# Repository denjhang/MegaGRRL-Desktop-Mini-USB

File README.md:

# MegaGRRL-Desktop-Mini-USB
 I have been using the desktop version of MegaGRRL for 4 years. As my PCB drawing skills improve, I have the confidence to realize all my ideas and changes. This version is based on the Type-C version and includes a lot of practical modifications.Note that for convenience, I only modified the PCB and not the schematic.    
The latest version: MegaGRRL Desktop DJ V0.5.  
It has been hardware verified and can be used.  
## Improvements of Type-C version :  
1. Use CH340C to replace CH340G to save crystal  
2. Use 2SC1815 to replace diode to get full CH340 serial port function (SPFM Lite compatibility)  
3. PCA9634D is difficult to buy, replaced with PCA9634PW.  
4. Use Type-C to replace USB-B.
5. Remaining issue: The solder pad of the 3.5mm headphone jack is too small.  
 ## Details of improvements to my version :   
1. Delete the 7805, 78M33, and other antique LDO step-down chips, as well as the huge heat sink, which are inefficient and generate a lot of heat. I used a newly designed SPFM Lite power supply circuit to replace it.  
2. Use an isolated voltage regulator module such as IB0905/0505S to achieve step-down/regulation, so the PCB currently supports 5V or 9V input, depending on the model of the voltage regulator module. B0905/0505 can be easily obtained on AliExpress. These voltage regulator modules work well on SPFM Lite, with very little power supply noise, which can further improve the sound quality.(Outdated)  
3. Delete MOSFETs such as IRF9530, which are huge and too retro.  
4. Use F0805 to protect the power circuit.  
5. Use a strong PS-22E05 (A04) self-locking switch to replace the original small switch to extend the life of the power button.  
6. All micro switches use white patch 6*6 silicone buttons, which do not require circuit modification and can significantly improve the user experience. The original micro switches made my hands hurt.
7. Because some buyers reported that the main volume potentiometer was easily damaged during transportation, I replaced it with RK097 B10K. RK097 is smaller and more robust, and the entire potentiometer is plastic-sealed, which is more reliable.  
8. Delete the 3296 potentiometer.  
9. In order to make the SN76489 volume adjustable, add an RK097 to adjust its volume, and replace R6/R8 with 47K.  
10. Replace the difficult-to-solder Type-C with Mini-USB.  
11. Restore natalie's silk screen art, obtained by reverse engineering the original desktop motherboard. (Actually not necessary)  
12. Double-layer square hole IC socket ensures good connection and service life. (No need to modify the PCB)  
13. Solder the round hole female header first in RN2 and then insert the resistor (no need to modify the PCB) to facilitate mass production and upload factory firmware.  
14. Add my silk screen art "Denjhang's OSHW"  
15. Optional self-ejecting SD card slot or self-ejecting TF card slot, more flexible to choose the type of memory card, protecting the memory card while further improving the user experience.  
16. Use "Mini560" high efficiency DC-DC step-down module to replace B0905/0505, it works very well so far, supports 9/12V input, and generates almost no heat. Mini560 can be easily purchased at Alex and is cheap.
17. Use the correct PJ-306/3F07 headphone jack package to replace the incorrect package in the Type-C version.
18. Added keyboard connector. Can be used to connect Cherry switches, MegaDrive controllers, wireless remote controls, etc. It can also be connected to the top keyboard of the acrylic case.  
 ## To do  
1. Design and make the acrylic shell, which is done by Xiaohao Studio (completed)  
2. Design a new MegaGRRL-modular motherboard to completely separate the data and analog lines and reduce interference noise. (completed)  
3. USB/DC dual power supply, refer to SPFM Lite circuit (completed)  
4. Compatible with RE:Birth module. (completed)  
5. Add battery interface. (completed)

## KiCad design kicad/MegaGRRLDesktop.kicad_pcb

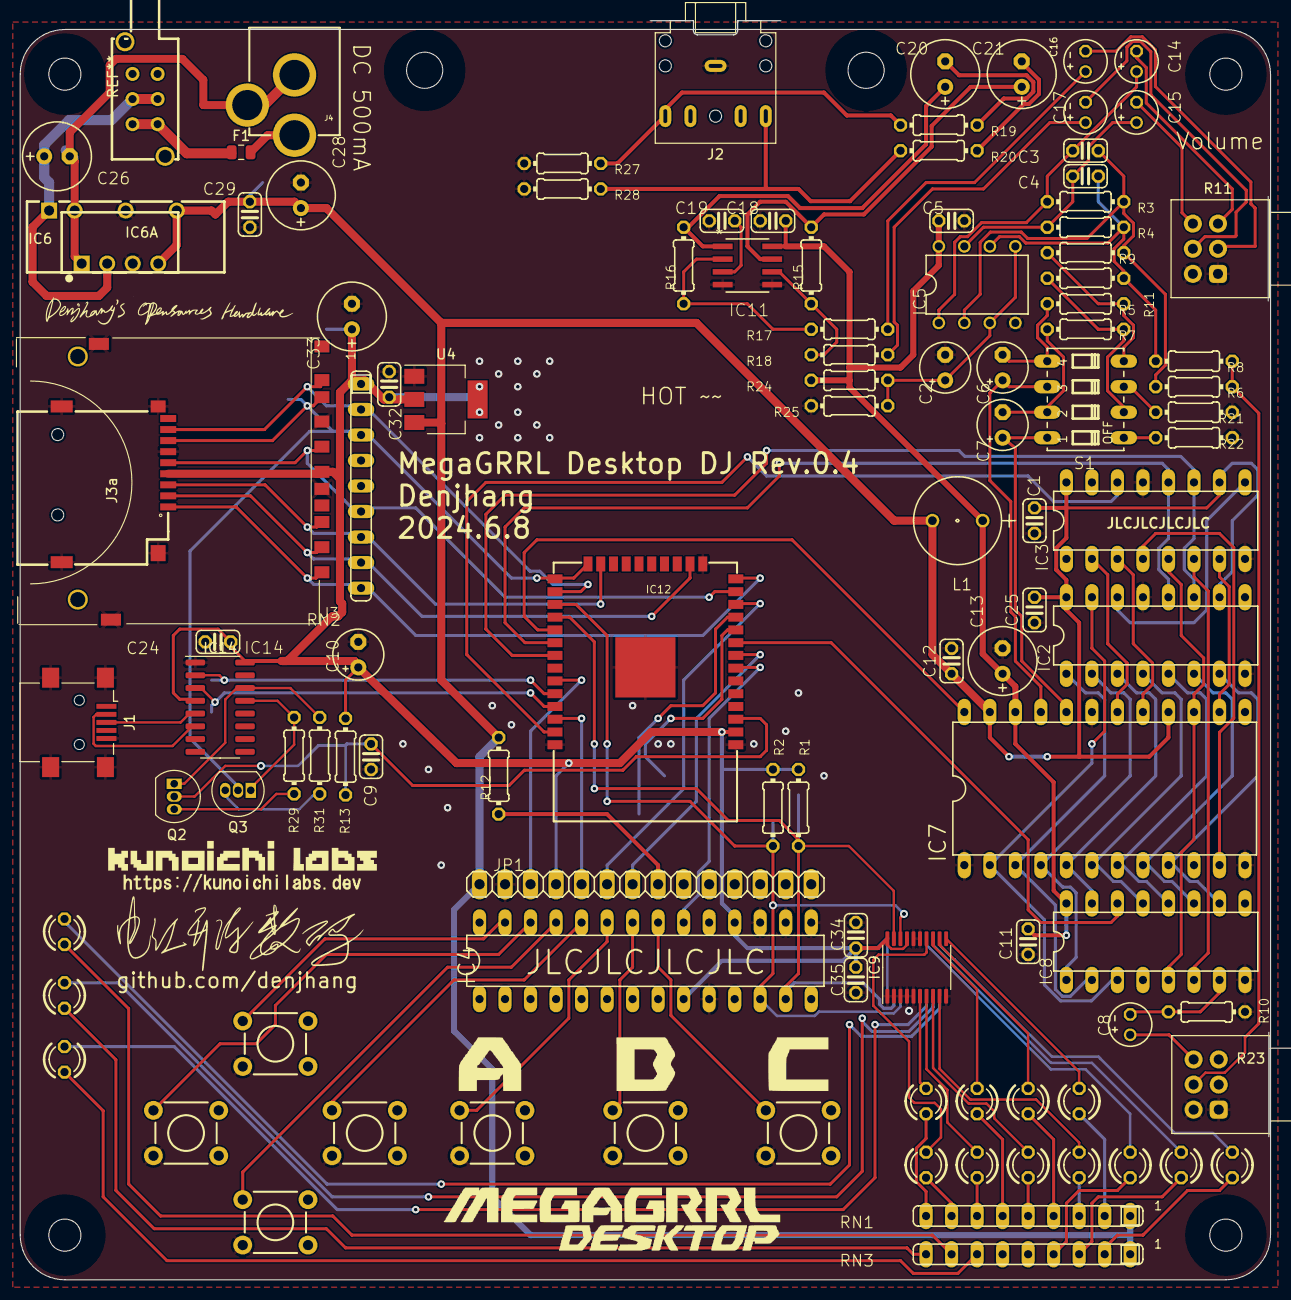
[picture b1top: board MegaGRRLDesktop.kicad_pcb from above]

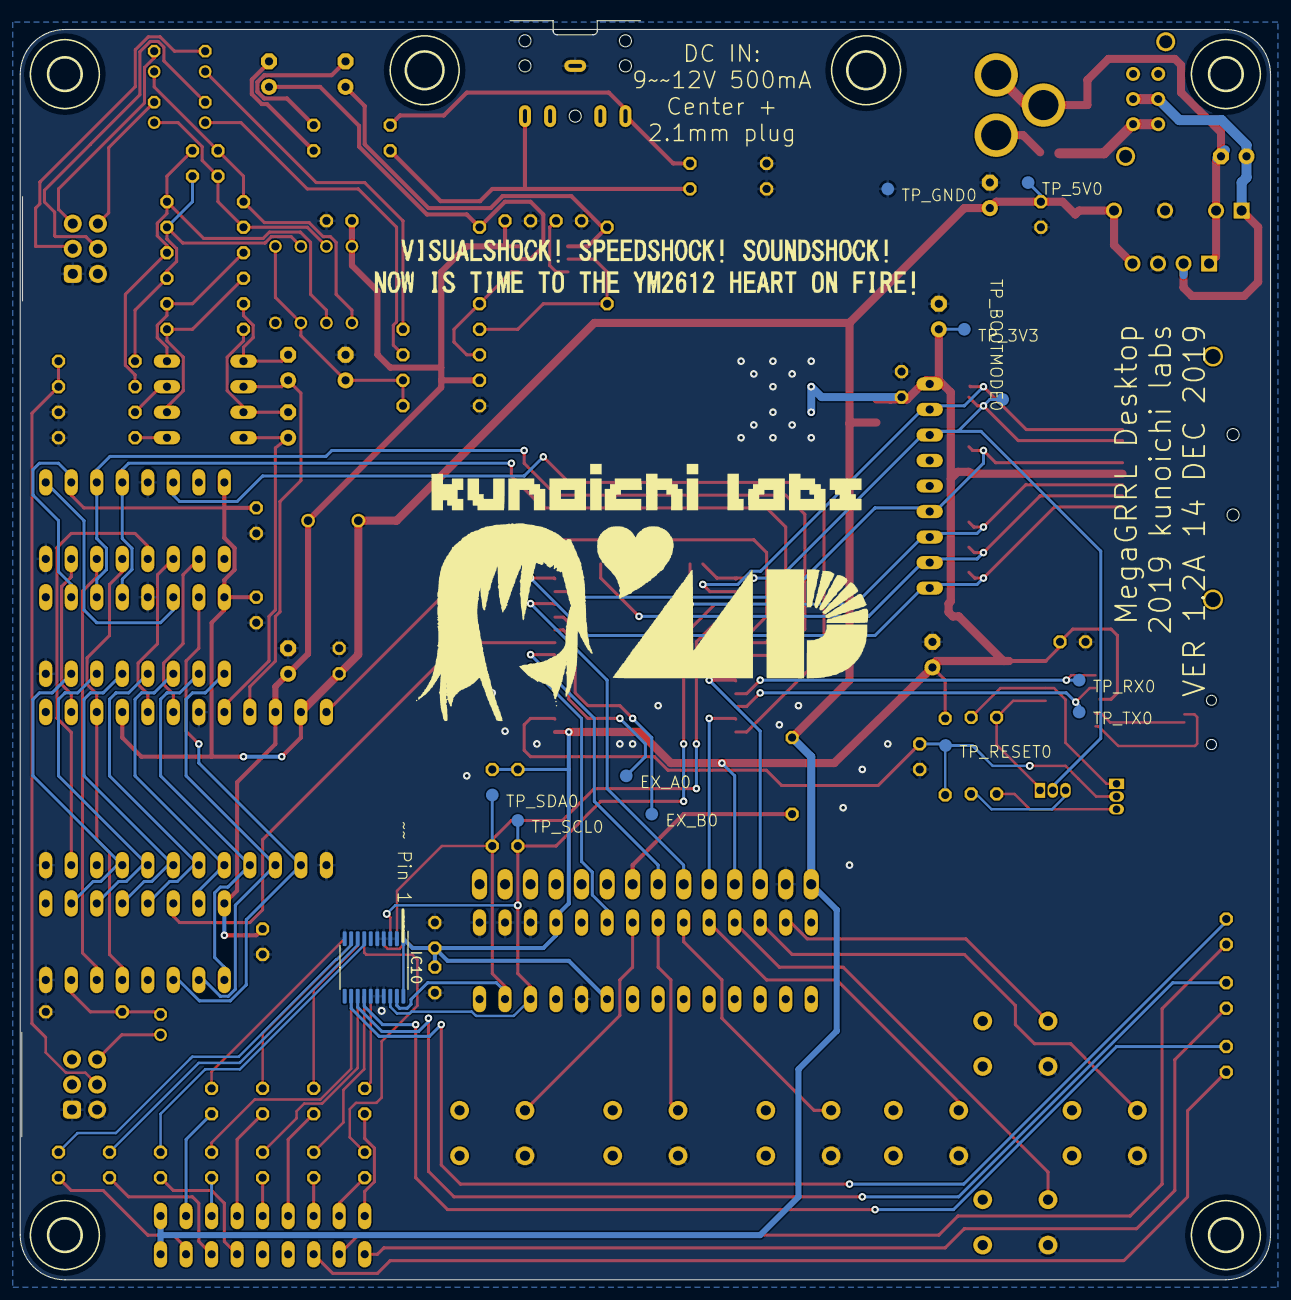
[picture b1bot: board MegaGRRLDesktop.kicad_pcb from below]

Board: 2 copper layers, 124.5 x 125.3 mm, 125 parts (18 on the bottom side), 118 nets.

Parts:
C1, C5, C9, C11, C12, C18, C19, C24, C25, C29, C32, C34, C35: 0.1uF; C025-024X044
C2, C6, C7, C10: 10uF; E2,5-5
C3, C4: 120pF; C025-024X044
C8, C14, C15, C16, C17: 1uF; E2-4
C13: 330uF; E2,5-7
C20, C21, C26, C28, C33: 100uF; E2,5-7
EX_A0: B1,27
EX_B0: B1,27
F1: Fuse_0805_2012Metric
H3, H4, H7, H8: MOUNT-HOLE3.2; 3,2
H5, H6: MOUNT-HOLE3.6; 3,6
IC2, IC3: 74HCT595N; DIL16
IC4: MCP23017SP; DIL28-3
IC5: NE5532N; DIL08
IC6: std:a4c6558b222b489b868198a352481a86; PWRM-TH_B0505S-3WR2
IC6A: std:44d60e1deb274ae4bbd12617d1f88879; PWRM-TH_BXXXXS-1W
IC7: YM2612
IC8: SN76489
IC9, IC10: PCA9634PW; TSSOP-20_4.4x6.5mm_P0.65mm
IC11: TPA6111A2DR; D8
IC12: ESP-WROOM-32ESP-WROOM-32-NO-RF; ESP-WROOM-32-NO-RF
IC14: CH340C; SOIC-16_3.9x9.9mm_P1.27mm
J1: USB_B_Mini; USB_Mini-B_Lumberg_2486_01_Horizontal
J2: 35RAPC4BHN2; Jack_3.5mm_CUI_SJ1-3525N_Horizontal
J3: 2041021-3; SD-106M
J3a: std:8630a74813a14cdca67e7b05dd5d2bc3; TF-SMD_TF-PUSH
J4: POWER_JACK; POWER_JACK_PTH
JP1: ILI9341_2_4
L1: RL622-101K-RC; RL622_SERIES
LED1, LED2, LED3, LED4, LED5, LED6, LED7, LED8, LED9, LED10, LED11, LED12, LED13, LED14: LED3MM
Q2, Q3: 2SC1815; TO-92_Inline
R1, R2, R10, R21, R22: 2k2; 0204_7
R3, R4: 82k; 0204_7
R5, R7: 47k; 0204_7
R6, R8: 47K; 0204_7
R9, R11: 5k6; 0204_7
R11#2, R23: Potentiometer_Alps_RK097_Dual_Horizontal
R12: 100R; 0204_7
R13, R17, R18, R27, R28, R29, R31: 10k; 0204_7
R15, R16: 15k; 0204_7
R19, R20: 10R; 0204_7
R24, R25: 100k; 0204_7
RN1, RN3: 1k; SIL9
RN2: 10k; SIL9
S1: DIP04S
SWA0: MOMENTARY-SWITCH-SPST-PTH-6.0MM; TACTILE_SWITCH_PTH_6.0MM
SWB0: MOMENTARY-SWITCH-SPST-PTH-6.0MM; TACTILE_SWITCH_PTH_6.0MM
SWC0: MOMENTARY-SWITCH-SPST-PTH-6.0MM; TACTILE_SWITCH_PTH_6.0MM
SWDOWN0: MOMENTARY-SWITCH-SPST-PTH-6.0MM; TACTILE_SWITCH_PTH_6.0MM
SWLEFT0: MOMENTARY-SWITCH-SPST-PTH-6.0MM; TACTILE_SWITCH_PTH_6.0MM
SWRIGHT0: MOMENTARY-SWITCH-SPST-PTH-6.0MM; TACTILE_SWITCH_PTH_6.0MM
SWUP0: MOMENTARY-SWITCH-SPST-PTH-6.0MM; TACTILE_SWITCH_PTH_6.0MM
TP_3V3, TP_5V0: B1,27
TP_BOOTMODE0: B1,27
TP_GND0: B1,27
TP_RESET0: B1,27
TP_RX0: B1,27
TP_SCL0: B1,27
TP_SDA0: B1,27
TP_TX0: B1,27
U4: AMS1117-3.3V; SOT-223

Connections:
+3V3: C10.+, C24.1, C32.1, C33.+, C34.1, C35.1, IC4.9 (VDD), IC4.18 (~RESET), IC9.17 (A6), IC9.20 (VDD), IC10.1 (A0), IC10.20 (VDD), IC12.2 (3V3), IC14.4 (V3), IC14.16 (VCC), J3.4, J3a.4, JP1.4, R1.2, R2.2, R13.2, RN2.1, TP_3V3.TP, U4.2 (OUT), U4.4 (TAB)
+5V: C1.1, C12.1, C25.1, C28.+, C29.1, IC2.10 (SCL), IC2.16 (VCC), IC3.10 (SCL), IC3.16 (VCC), IC6.6, IC6A.4, IC7./RD, IC7.VCC, JP1.1, L1.2, R12.2, RN1.1, RN3.1, TP_5V0.TP, U4.3 (IN)
+5V/2: C5.1, C11.1, C13.+, C18.1, IC5.8 (V+), IC7.AVCC, IC8.VCC, IC11.8 (VDD), L1.1, R24.2
+12V: C26.+, IC6.1, IC6A.2
/Audio/AUDIO_LINEL: C16.+, R17.1
/Audio/AUDIO_LINER: C17.+, R18.1
/Keys/KEY_A: IC4.23 (GPA2), SWA0.1
/Keys/KEY_B: IC4.22 (GPA1), SWB0.1
/Keys/KEY_C: IC4.21 (GPA0), SWC0.1
/Keys/KEY_DOWN: IC4.25 (GPA4), SWDOWN0.1
/Keys/KEY_LEFT: IC4.26 (GPA5), SWLEFT0.1
/Keys/KEY_RIGHT: IC4.24 (GPA3), SWRIGHT0.1
/Keys/KEY_UP: IC4.27 (GPA6), SWUP0.1
/LED drivers/FM1: IC9.14 (LED7), LED1.K (C)
/LED drivers/FM1N: LED1.A, RN1.8
/LED drivers/FM2: IC9.7 (LED1), LED2.K (C)
/LED drivers/FM2N: LED2.A, RN1.7
/LED drivers/FM3: IC9.8 (LED2), LED3.K (C)
/LED drivers/FM3N: LED3.A, RN1.5
/LED drivers/FM4: IC9.9 (LED3), LED4.K (C)
/LED drivers/FM4N: LED4.A, RN1.3
/LED drivers/FM5: IC10.7 (LED1), LED5.K (C)
/LED drivers/FM5N: LED5.A, RN3.4
/LED drivers/FM6: IC10.8 (LED2), LED6.K (C)
/LED drivers/FM6N: LED6.A, RN3.3
/LED drivers/FMS: IC10.9 (LED3), LED7.K (C)
/LED drivers/FMSN: LED7.A, RN3.2
/LED drivers/PSG1: IC9.6 (LED0), LED8.K (C)
/LED drivers/PSG1N: LED8.A, RN1.9
/LED drivers/PSG2: IC9.13 (LED6), LED9.K (C)
/LED drivers/PSG2N: LED9.A, RN1.6
/LED drivers/PSG3: IC9.12 (LED5), LED10.K (C)
/LED drivers/PSG3N: LED10.A, RN1.4
/LED drivers/PSGS: IC9.11 (LED4), LED11.K (C)
/LED drivers/PSGSN: LED11.A, RN1.2
/LED drivers/USERA: IC10.12 (LED5), LED12.K (C)
/LED drivers/USERAN: LED12.A, RN3.8
/LED drivers/USERB: IC10.13 (LED6), LED13.K (C)
/LED drivers/USERBN: LED13.A, RN3.9
/LED drivers/USERC: IC10.14 (LED7), LED14.K (C)
/LED drivers/USERCN: LED14.A, RN3.7
/MCU & interface/ESP32_RESET: C9.1, IC12.3 (EN), Q2.2 (C), R13.1, TP_RESET0.TP
/MCU & interface/LCD_CLK: IC12.8 (IO32), JP1.7
/MCU & interface/LCD_DC: IC12.36 (IO22), JP1.5
/MCU & interface/LCD_MOSI: IC12.12 (IO27), JP1.6
/MCU & interface/LCD_/CS: IC12.33 (IO21), JP1.3
/MCU & interface/RXD: IC12.34 (RXD0), IC14.2 (TXD), TP_RX0.TP
/MCU & interface/SD_CLK: IC12.13 (IO14), J3.5, J3a.5, RN2.6
/MCU & interface/SD_CMD: IC12.23 (IO15), J3.2, J3a.3, RN2.7
/MCU & interface/SD_D0: IC12.24 (IO2), IC12.25 (IO0), J3.7, J3a.7, Q3.2 (C), RN2.3, TP_BOOTMODE0.TP
/MCU & interface/SD_D1: IC12.26 (IO4), J3.8, J3a.8, RN2.2
/MCU & interface/SD_D2: IC12.14 (IO12), J3.9, J3a.1, RN2.9
/MCU & interface/SD_D3: IC12.16 (IO13), J3.1, J3a.2, RN2.8
/MCU & interface/TXD: IC12.35 (TXD0), IC14.3 (RXD), TP_TX0.TP
/Sound chips & bus/A0: IC3.3 (QD), IC7.A0
/Sound chips & bus/A1: IC3.2 (QC), IC7.A1
/Sound chips & bus/D0: IC2.15 (QA), IC7.D0, IC8.D7
/Sound chips & bus/D1: IC2.1 (QB), IC7.D1, IC8.D6
/Sound chips & bus/D2: IC2.2 (QC), IC7.D2, IC8.D5
/Sound chips & bus/D3: IC2.3 (QD), IC7.D3, IC8.D4
/Sound chips & bus/D4: IC2.4 (QE), IC7.D4, IC8.D3
/Sound chips & bus/D5: IC2.5 (QF), IC7.D5, IC8.D2
/Sound chips & bus/D6: IC2.6 (QG), IC7.D6, IC8.D1
/Sound chips & bus/D7: IC2.7 (QH), IC7.D7, IC8.D0
/Sound chips & bus//CS_FM: IC3.7 (QH), IC7./CS
/Sound chips & bus//CS_PSG: IC3.6 (QG), IC8./OE
/Sound chips & bus//IC: IC3.4 (QE), IC7./IC
/Sound chips & bus//WR: IC3.5 (QF), IC7./WR, IC8./WE
AUDIO_FML: C6.+, IC7.MOL, S1.6 (2)
AUDIO_FMR: C7.+, IC7.MOR, S1.8 (2)
AUDIO_PSG: C8.-, IC8.SND_OUT, R10.1
CLK_FM: IC7.M, IC12.29 (IO5)
CLK_PSG: IC8.CLOCK, IC12.9 (IO33)
GND: C1.2, C2.-, C5.2, C9.2, C10.-, C11.2, C12.2, C13.-, C18.2, C19.2, C24.2, C25.2, C28.-, C29.2, C32.2, C33.-, C34.2, C35.2, IC2.8 (GND), IC2.13 (G), IC3.8 (GND), IC3.13 (G), IC4.10 (VSS), IC4.15 (A0), IC4.16 (A1), IC4.17 (A2), IC5.4 (V-), IC6.4, IC6A.3, IC7.AGND, IC7.GND@1, IC7.GND@2, IC8.GND, IC9.1 (A0), IC9.2 (A1), IC9.3 (A2), IC9.4 (A3), IC9.5 (A4), IC9.10 (VSS), IC9.15 (OE), IC9.16 (A5), IC10.2 (A1), IC10.3 (A2), IC10.4 (A3), IC10.5 (A4), IC10.10 (VSS), IC10.15 (OE), IC10.16 (A5), IC10.17 (A6), IC11.4 (GND), IC11.5 (SHUTDOWN), IC12.1 (GND@1), IC12.15 (GND@15), IC12.38 (GND@38), IC12.GND, IC14.1 (GND), J1.5 (GND), J1.6 (Shield), J2.S, J3.3, J3.6, J3.12 (COMMON_GROUND_1), J3.13 (COMMON_GROUND_2), J3a.6, J3a.10, J3a.11, J3a.12, J3a.13, JP1.2, R10.2, R11#2.1, R11#2.4, R21.1, R22.1, R23.1, R23.4, R25.1, R27.1, R28.1, SWA0.3 (2), SWB0.3 (2), SWC0.3 (2), SWDOWN0.3 (2), SWLEFT0.3 (2), SWRIGHT0.3 (2), SWUP0.3 (2), TP_GND0.TP, U4.1 (GND)
GND-IN: C26.-, IC6.2, IC6A.1, J4.GND, J4.GNDBREAK
KEY_INT: IC4.20 (INTA), IC12.7 (IO35)
unnamed: C8.+, R23.6
unnamed: C20.-, R19.1
unnamed: C21.-, R20.1
unnamed: F1.2, J4.PWR
unnamed: IC2.14 (SER), IC3.9 (QH*)
unnamed: C3.1, IC5.2 (-IN), R3.2, R6.1, R9.1
unnamed: C3.2, C14.+, IC5.1 (OUT), R3.1
unnamed: C4.1, IC5.6 (-IN), R4.2, R8.1, R11.1
unnamed: C4.2, C15.+, IC5.7 (OUT), R4.1
unnamed: C19.1, IC11.3 (BYPASS)
unnamed: IC11.2 (IN1-), R16.1, R17.2
unnamed: IC11.6 (IN2-), R15.1, R18.2
unnamed: C20.+, IC11.1 (VO1), R16.2
unnamed: C21.+, IC11.7 (VO2), R15.2
unnamed: EX_A0.TP, IC12.10 (IO25)
unnamed: EX_B0.TP, IC12.11 (IO26)
unnamed: IC14.5 (UD+), J1.3 (D+)
unnamed: IC14.6 (UD-), J1.2 (D-)
unnamed: IC14.13 (~DTR), Q3.1 (E), R29.1
unnamed: IC14.14 (~RTS), Q2.1 (E), R31.1
unnamed: J2.R, R20.2, R28.2
unnamed: J2.T, R19.2, R27.2
unnamed: JP1.8, R12.1
unnamed: Q2.3 (B), R29.2
unnamed: Q3.3 (B), R31.2
unnamed: C14.-, R11#2.3
unnamed: C16.-, R11#2.2
unnamed: C15.-, R11#2.6
unnamed: C17.-, R11#2.5
unnamed: R22.2, S1.1
unnamed: R6.2, R8.2, R23.5
unnamed: R7.1, R11.2, S1.2 (1)
unnamed: C7.-, R7.2, S1.7 (2)
unnamed: R21.2, S1.3 (1)
unnamed: R5.1, R9.2, S1.4 (1)
unnamed: C6.-, R5.2, S1.5 (2)
SCL: IC4.12 (SCL), IC9.18 (SCL), IC10.18 (SCL), IC12.27 (IO16), R2.1, TP_SCL0.TP
SDA: IC4.13 (SDA), IC9.19 (SDA), IC10.19 (SDA), IC12.28 (IO17), R1.1, TP_SDA0.TP
SHCLK: IC2.11 (SCK), IC3.11 (SCK), IC12.31 (IO19)
SHDATA: IC3.14 (SER), IC12.37 (IO23)
SHSTO: IC2.12 (RCK), IC3.12 (RCK), IC12.30 (IO18)
VBIAS: C2.+, IC5.3 (+IN), IC5.5 (+IN), R24.1, R25.2

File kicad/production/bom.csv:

Designator,Footprint,Quantity,Value,LCSC Part #
"C1, C11, C12, C18, C19, C24, C25, C29, C32, C34, C35, C5, C9",C025-024X044,13,0.1uF,
"C10, C2, C6, C7","E2,5-5",4,10uF,
C13,"E2,5-7",1,330uF,
"C14, C15, C16, C17, C8",E2-4,5,1uF,
"C20, C21, C26, C28, C33","E2,5-7",5,100uF,
"C3, C4",C025-024X044,2,120pF,
"EX_A0, EX_B0, TP_3V3, TP_5V0, TP_BOOTMODE0, TP_GND0, TP_RESET0, TP_RX0, TP_SCL0, TP_SDA0, TP_TX0","B1,27",11,"TPB1,27",
F1,0805,1,Fuse_0805_2012Metric,
"H3, H4, H7, H8","3,2",4,MOUNT-HOLE3.2,
"H5, H6","3,6",2,MOUNT-HOLE3.6,
"IC10, IC9",TSSOP-20_4.4x6.5mm_P0.65mm,2,PCA9634PW,
IC11,D8,1,TPA6111A2DR,
IC12,ESP-WROOM-32-NO-RF,1,ESP-WROOM-32ESP-WROOM-32-NO-RF,
IC14,SOIC-16_3.9x9.9mm_P1.27mm,1,CH340C,
"IC2, IC3",DIL16,2,74HCT595N,
IC4,DIL28-3,1,MCP23017SP,
IC5,DIL08,1,NE5532N,
IC6,PWRM-TH_B0505S-3WR2,1,std:a4c6558b222b489b868198a352481a86,
IC6A,PWRM-TH_BXXXXS-1W,1,std:44d60e1deb274ae4bbd12617d1f88879,
IC7,YM2612,1,YM2612,
IC8,SN76489,1,SN76489,
J1,USB_Mini-B_Lumberg_2486_01_Horizontal,1,USB_B_Mini,
J2,Jack_3.5mm_CUI_SJ1-3525N_Horizontal,1,35RAPC4BHN2,
J3,SD-106M,1,2041021-3,
J3a,TF-SMD_TF-PUSH,1,std:8630a74813a14cdca67e7b05dd5d2bc3,
J4,POWER_JACK_PTH,1,POWER_JACK,
JP1,ILI9341_2_4,1,ILI9341_2_4,
L1,RL622_SERIES,1,RL622-101K-RC,
"LED1, LED10, LED11, LED12, LED13, LED14, LED2, LED3, LED4, LED5, LED6, LED7, LED8, LED9",LED3MM,14,LED3MM,
"Q2, Q3",TO-92_Inline,2,2SC1815,
"R1, R10, R2, R21, R22",0204_7,5,2k2,
"R11_2, R9",0204_7,2,5k6,
"R11, R23",Potentiometer_Alps_RK097_Dual_Horizontal,2,Potentiometer_Alps_RK097_Dual_Horizontal,
R12,0204_7,1,100R,
"R13, R17, R18, R27, R28, R29, R31",0204_7,7,10k,
"R15, R16",0204_7,2,15k,
"R19, R20",0204_7,2,10R,
"R24, R25",0204_7,2,100k,
"R3, R4",0204_7,2,82k,
"R5, R6, R7, R8",0204_7,4,47k,
"RN1, RN3",SIL9,2,1k,
RN2,SIL9,1,10k,
S1,DIP04S,1,DIP04S,
"SWA0, SWB0, SWC0, SWDOWN0, SWLEFT0, SWRIGHT0, SWUP0",TACTILE_SWITCH_PTH_6.0MM,7,MOMENTARY-SWITCH-SPST-PTH-6.0MM,
U4,SOT-223,1,AMS1117-3.3V,

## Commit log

2024-06-09 0.47
2024-07-07 2024.7.7
2024-07-11 2024.7.11
